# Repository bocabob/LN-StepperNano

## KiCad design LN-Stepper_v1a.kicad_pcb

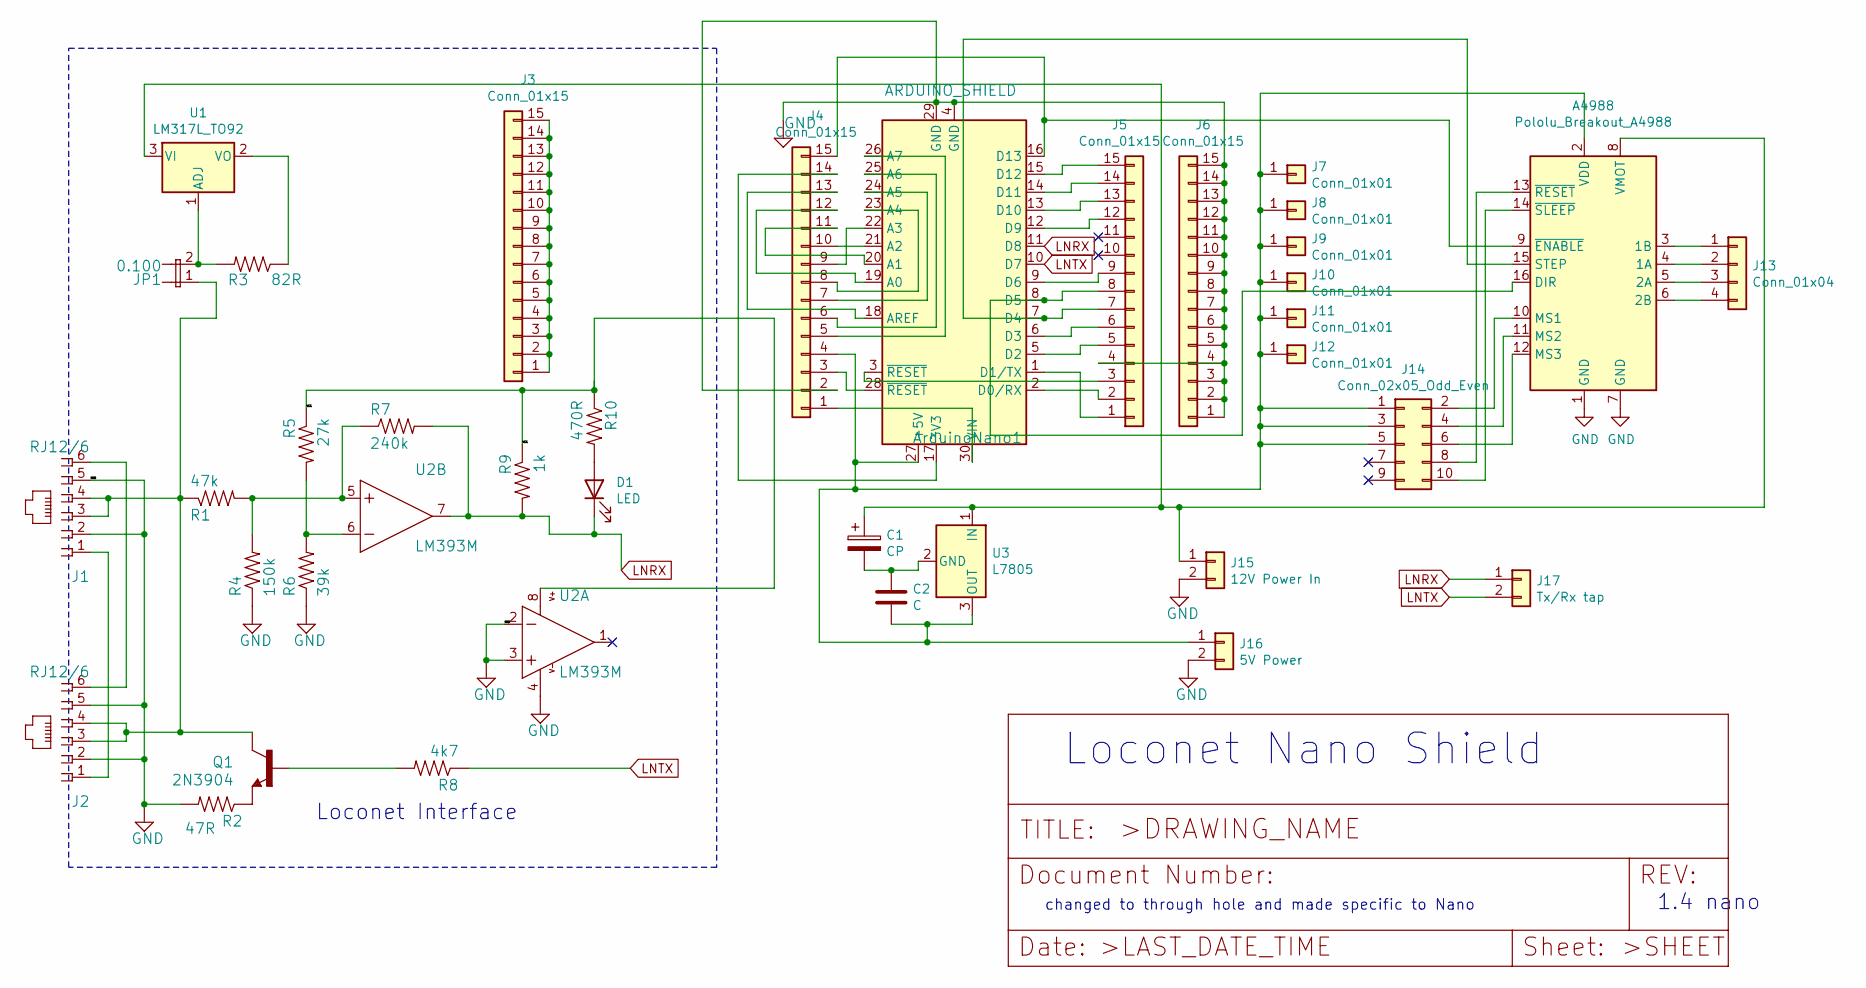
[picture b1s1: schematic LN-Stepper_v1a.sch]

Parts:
A4988: Pololu_Breakout_A4988; Pololu_Breakout-16_15.2x20.3mm
ArduinoNano1: ARDUINO_SHIELD; Arduino_Nano
C1: CP; CP_Radial_D8.0mm_P3.80mm
C2: C; CP_Radial_Tantal_D4.5mm_P5.00mm
D1: LED; LED_D5.0mm
J1, J2: RJ12/6; RJ25-PANEL
J3, J4, J5, J6: Conn_01x15; PinHeader_1x15_P2.54mm_Vertical
J7, J8, J9, J10, J11, J12: Conn_01x01; PinHeader_1x01_P2.54mm_Vertical
J13: Conn_01x04; PinSocket_1x04_P2.54mm_Vertical
J14: Conn_02x05_Odd_Even; PinHeader_2x05_P2.54mm_Vertical
J15: 12V Power In; BarrelJack_Horizontal
J16: 5V Power; TerminalBlock_Phoenix_PT-1,5-2-3.5-H_1x02_P3.50mm_Horizontal
J17: Tx/Rx tap; PinHeader_1x02_P2.54mm_Vertical
JP1: 0.100; 1X02_LOCK
Q1: 2N3904; TO-92L_Inline
R1: 47k; R_Axial_DIN0207_L6.3mm_D2.5mm_P7.62mm_Horizontal
R2: 47R; R_Axial_DIN0207_L6.3mm_D2.5mm_P7.62mm_Horizontal
R3: 82R; R_Axial_DIN0207_L6.3mm_D2.5mm_P2.54mm_Vertical
R4: 150k; R_Axial_DIN0207_L6.3mm_D2.5mm_P7.62mm_Horizontal
R5: 27k; R_Axial_DIN0207_L6.3mm_D2.5mm_P7.62mm_Horizontal
R6: 39k; R_Axial_DIN0207_L6.3mm_D2.5mm_P7.62mm_Horizontal
R7: 240k; R_Axial_DIN0207_L6.3mm_D2.5mm_P7.62mm_Horizontal
R8: 4k7; R_Axial_DIN0207_L6.3mm_D2.5mm_P7.62mm_Horizontal
R9: 1k; R_Axial_DIN0207_L6.3mm_D2.5mm_P7.62mm_Horizontal
R10: 470R; R_Axial_DIN0207_L6.3mm_D2.5mm_P7.62mm_Horizontal
U1: LM317L_TO92; TO-92_Inline
U2: LM393M; DIP-8_W7.62mm_LongPads
U3: L7805; TO-220-3_Vertical

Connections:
/VCC: R5.1, R9.1, R10.1, U2.8 (V+)
GND: A4988.1 (GND), A4988.7 (GND), ArduinoNano1.4 (GND), ArduinoNano1.29 (GND), J1.2, J1.5, J2.2, J2.5, J4.2, J5.4, J6.1, J6.2, J6.3, J6.4, J6.5, J6.6, J6.7, J6.8, J6.9, J6.10, J6.11, J6.12, J6.13, J6.14, J6.15, J15.2, J16.2, R2.2, R4.1, R6.1, U2.2 (-IN), U2.3 (+IN), U2.4 (V-)
LNRX: ArduinoNano1.11 (D8), D1.1 (K), J17.1, R7.2, R9.2, U2.7 (OUT)
LNTX: ArduinoNano1.10 (D7), J17.2, R8.1
unnamed: A4988.2 (VDD), ArduinoNano1.27 (+5V), C2.2, J4.4, J7.1, J8.1, J9.1, J10.1, J11.1, J12.1, J14.1, J14.3, J14.5, J16.1, U3.3 (OUT)
unnamed: A4988.3 (1B), J13.1
unnamed: A4988.4 (1A), J13.2
unnamed: A4988.5 (2A), J13.3
unnamed: A4988.6 (2B), J13.4
unnamed: A4988.8 (VMOT), C1.1, J15.1, U1.3 (VI), U3.1 (IN)
unnamed: A4988.9 (~ENABLE), ArduinoNano1.16 (D13), J4.15
unnamed: A4988.10 (MS1), J14.2
unnamed: A4988.11 (MS2), J14.4
unnamed: A4988.12 (MS3), J14.6
unnamed: A4988.13 (~RESET), J14.8
unnamed: A4988.14 (~SLEEP), J14.10
unnamed: A4988.15 (STEP), ArduinoNano1.7 (D4), J5.7
unnamed: A4988.16 (DIR), ArduinoNano1.8 (D5), J5.8
unnamed: ArduinoNano1.1 (D1/TX), J5.1
unnamed: ArduinoNano1.2 (D0/RX), J5.2
unnamed: ArduinoNano1.3 (~RESET), J5.3
unnamed: ArduinoNano1.5 (D2), J5.5
unnamed: ArduinoNano1.6 (D3), J5.6
unnamed: ArduinoNano1.9 (D6), J5.9
unnamed: ArduinoNano1.12 (D9), J5.12
unnamed: ArduinoNano1.13 (D10), J5.13
unnamed: ArduinoNano1.14 (D11), J5.14
unnamed: ArduinoNano1.15 (D12), J5.15
unnamed: ArduinoNano1.17 (3V3), J4.14
unnamed: ArduinoNano1.18 (AREF), J4.13
unnamed: ArduinoNano1.19 (A0), J4.12
unnamed: ArduinoNano1.20 (A1), J4.11
unnamed: ArduinoNano1.21 (A2), J4.10
unnamed: ArduinoNano1.22 (A3), J4.9
unnamed: ArduinoNano1.23 (A4), J4.8
unnamed: ArduinoNano1.24 (A5), J4.7
unnamed: ArduinoNano1.25 (A6), J4.6
unnamed: ArduinoNano1.26 (A7), J4.5
unnamed: ArduinoNano1.28 (~RESET), J4.3
unnamed: ArduinoNano1.30 (VIN), J4.1
unnamed: C1.2, C2.1, U3.2 (GND)
unnamed: D1.2 (A), R10.2
unnamed: J1.1, J2.1
unnamed: J1.3, J1.4, J2.3, J2.4, JP1.1, Q1.3 (C), R1.1
unnamed: J1.6, J2.6
unnamed: J3.1, J3.2, J3.3, J3.4, J3.5, J3.6, J3.7, J3.8, J3.9, J3.10, J3.11, J3.12, J3.13, J3.14, J3.15
unnamed: JP1.2, R3.2, U1.1 (ADJ)
unnamed: Q1.1 (B), R8.2
unnamed: Q1.2 (E), R2.1
unnamed: R1.2, R4.2, R7.1, U2.5 (+IN)
unnamed: R3.1, U1.2 (VO)
unnamed: R5.2, R6.2, U2.6 (-IN)

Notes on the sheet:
Loconet Interface
Loconet Nano Shield
1.4 nano
changed to through hole and made specific to Nano

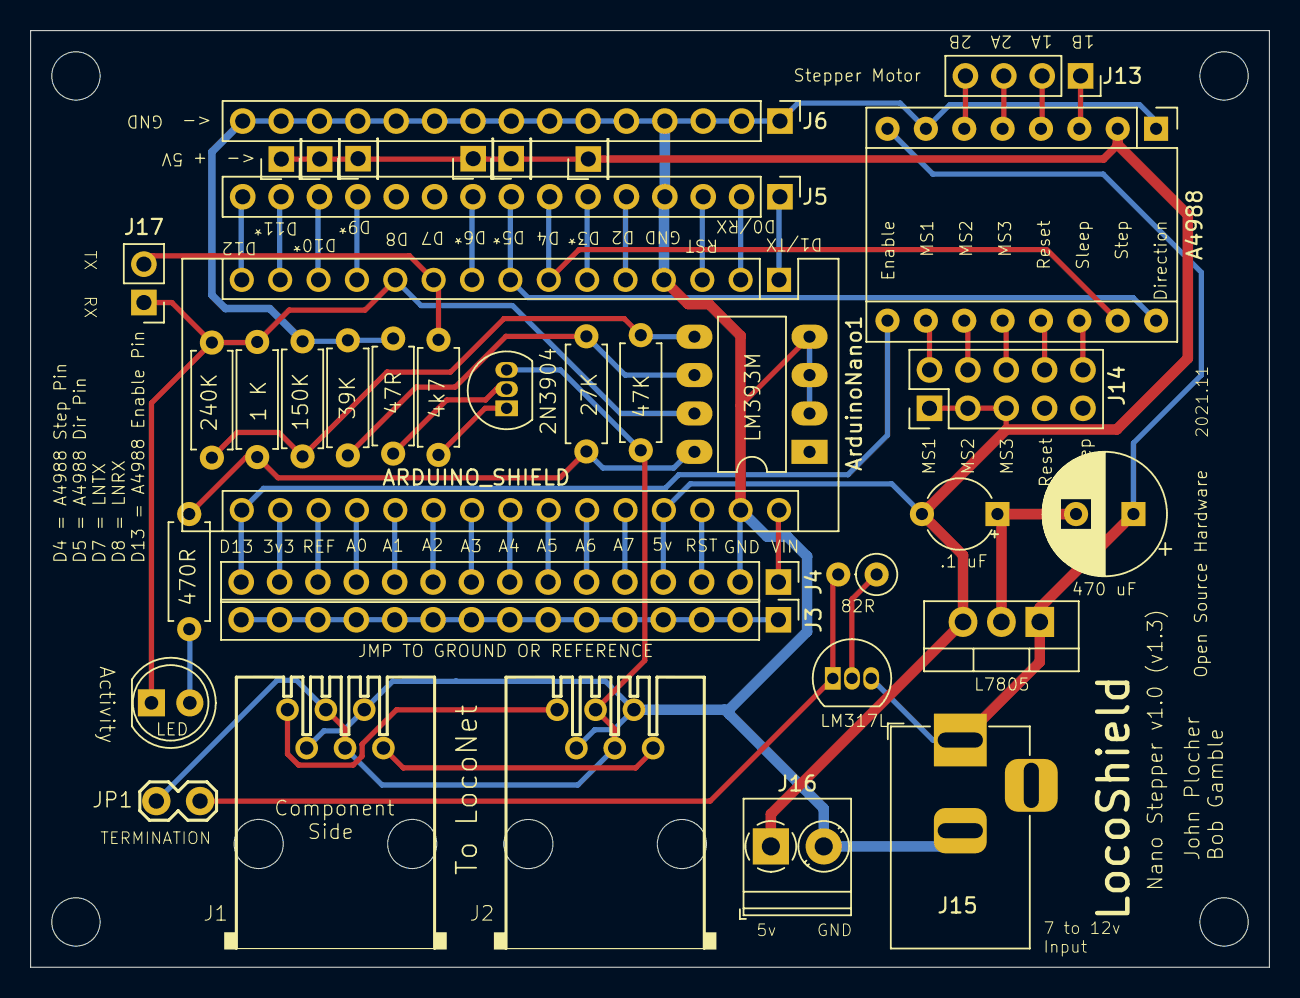
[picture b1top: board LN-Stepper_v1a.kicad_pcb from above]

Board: 2 copper layers, 82.0 x 62.0 mm, 37 parts (0 on the bottom side), 52 nets.

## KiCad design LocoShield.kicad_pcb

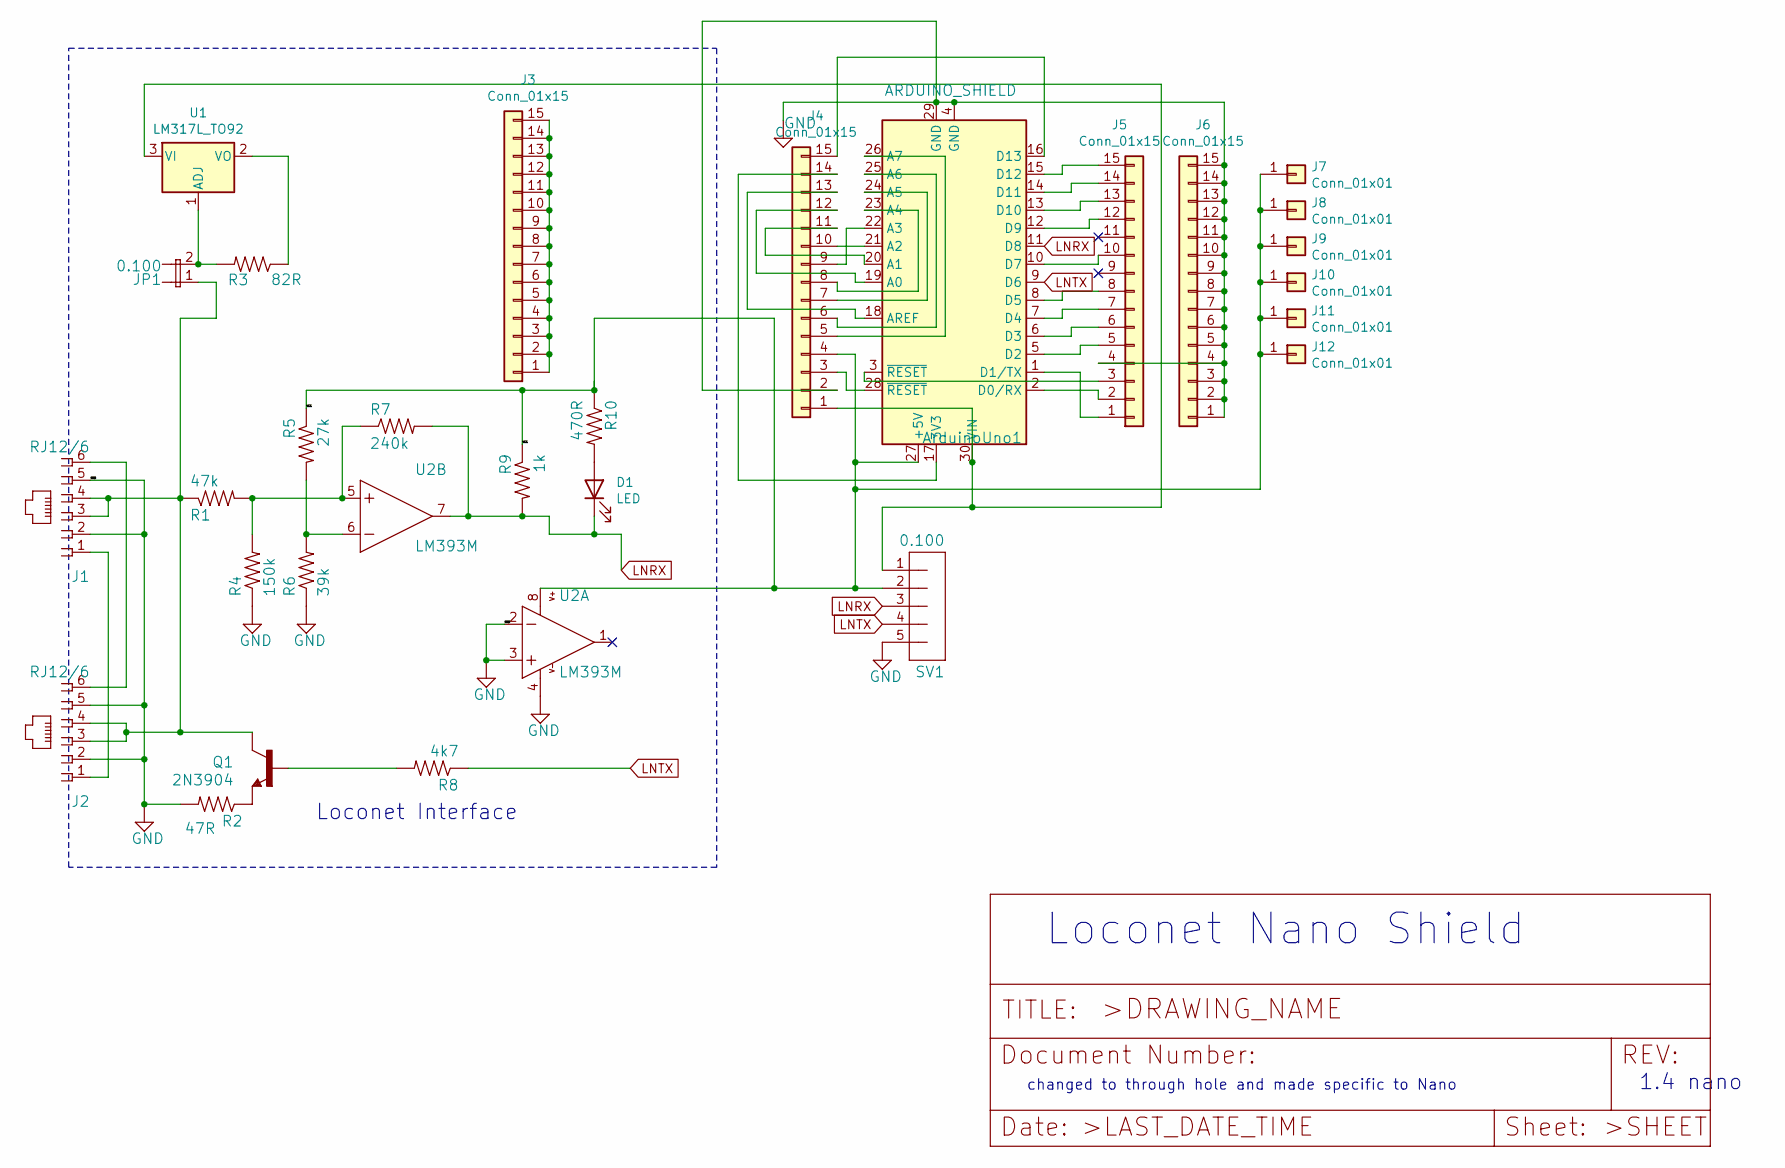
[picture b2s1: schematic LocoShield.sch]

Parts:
ArduinoUno1: ARDUINO_SHIELD; Arduino_Nano
D1: LED; LED_D5.0mm
J1, J2: RJ12/6; RJ25-PANEL
J3, J4, J5, J6: Conn_01x15; PinHeader_1x15_P2.54mm_Vertical
J7, J8, J9, J10, J11, J12: Conn_01x01; PinHeader_1x01_P2.54mm_Vertical
JP1: 0.100; 1X02_LOCK
Q1: 2N3904; TO-92L_Inline
R1: 47k; R_Axial_DIN0207_L6.3mm_D2.5mm_P2.54mm_Vertical
R2: 47R; R_Axial_DIN0207_L6.3mm_D2.5mm_P7.62mm_Horizontal
R3: 82R; R_Axial_DIN0207_L6.3mm_D2.5mm_P2.54mm_Vertical
R4: 150k; R_Axial_DIN0207_L6.3mm_D2.5mm_P7.62mm_Horizontal
R5: 27k; R_Axial_DIN0207_L6.3mm_D2.5mm_P7.62mm_Horizontal
R6: 39k; R_Axial_DIN0207_L6.3mm_D2.5mm_P7.62mm_Horizontal
R7: 240k; R_Axial_DIN0207_L6.3mm_D2.5mm_P7.62mm_Horizontal
R8: 4k7; R_Axial_DIN0207_L6.3mm_D2.5mm_P7.62mm_Horizontal
R9: 1k; R_Axial_DIN0207_L6.3mm_D2.5mm_P7.62mm_Horizontal
R10: 470R; R_Axial_DIN0207_L6.3mm_D2.5mm_P7.62mm_Horizontal
SV1: 0.100; MA05-1
U1: LM317L_TO92; TO-92_Inline
U2: LM393M; DIP-8_W7.62mm_LongPads

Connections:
/VCC: ArduinoUno1.27 (+5V), J4.4, J7.1, J8.1, J9.1, J10.1, J11.1, J12.1, R5.1, R9.1, R10.1, SV1.2, U2.8 (V+); also elsewhere on the board
GND: ArduinoUno1.4 (GND), ArduinoUno1.29 (GND), J1.2, J1.5, J2.2, J2.5, J4.2, J5.4, J6.1, J6.2, J6.3, J6.4, J6.5, J6.6, J6.7, J6.8, J6.9, J6.10, J6.11, J6.12, J6.13, J6.14, J6.15, R2.2, R4.1, R6.1, SV1.5, U2.2 (-IN), U2.3 (+IN), U2.4 (V-); also elsewhere on the board
LNRX: ArduinoUno1.11 (D8), D1.1 (K), R7.2, R9.2, SV1.3, U2.7 (OUT); also elsewhere on the board
LNTX: ArduinoUno1.9 (D6), R8.1, SV1.4; also elsewhere on the board
unnamed 4: ArduinoUno1.1 (D1/TX), J5.1; also elsewhere on the board
unnamed 5: ArduinoUno1.2 (D0/RX), J5.2; also elsewhere on the board
unnamed 6: ArduinoUno1.3 (~RESET), J5.3; also elsewhere on the board
unnamed 7: ArduinoUno1.5 (D2), J5.5; also elsewhere on the board
unnamed 8: ArduinoUno1.6 (D3), J5.6; also elsewhere on the board
unnamed 9: ArduinoUno1.7 (D4), J5.7; also elsewhere on the board
unnamed 10: ArduinoUno1.8 (D5), J5.8; also elsewhere on the board
unnamed 11: ArduinoUno1.10 (D7), J5.10; also elsewhere on the board
unnamed 12: ArduinoUno1.12 (D9), J5.12; also elsewhere on the board
unnamed 13: ArduinoUno1.13 (D10), J5.13; also elsewhere on the board
unnamed 14: ArduinoUno1.14 (D11), J5.14; also elsewhere on the board
unnamed 15: ArduinoUno1.15 (D12), J5.15; also elsewhere on the board
unnamed 16: ArduinoUno1.16 (D13), J4.15; also elsewhere on the board
unnamed 17: ArduinoUno1.17 (3V3), J4.14; also elsewhere on the board
unnamed 18: ArduinoUno1.18 (AREF), J4.13; also elsewhere on the board
unnamed 19: ArduinoUno1.19 (A0), J4.12; also elsewhere on the board
unnamed 20: ArduinoUno1.20 (A1), J4.11; also elsewhere on the board
unnamed 21: ArduinoUno1.21 (A2), J4.10; also elsewhere on the board
unnamed 22: ArduinoUno1.22 (A3), J4.9; also elsewhere on the board
unnamed 23: ArduinoUno1.23 (A4), J4.8; also elsewhere on the board
unnamed 24: ArduinoUno1.24 (A5), J4.7; also elsewhere on the board
unnamed 25: ArduinoUno1.25 (A6), J4.6; also elsewhere on the board
unnamed 26: ArduinoUno1.26 (A7), J4.5; also elsewhere on the board
unnamed 27: ArduinoUno1.28 (~RESET), J4.3; also elsewhere on the board
unnamed 28: ArduinoUno1.30 (VIN), J4.1, SV1.1, U1.3 (VI); also elsewhere on the board
unnamed: D1.2 (A), R10.2
unnamed: J1.1, J2.1
unnamed: J1.3, J1.4, J2.3, J2.4, JP1.1, Q1.3 (C), R1.1
unnamed: J1.6, J2.6
unnamed: J3.1, J3.2, J3.3, J3.4, J3.5, J3.6, J3.7, J3.8, J3.9, J3.10, J3.11, J3.12, J3.13, J3.14, J3.15
unnamed: JP1.2, R3.2, U1.1 (ADJ)
unnamed: Q1.1 (B), R8.2
unnamed: Q1.2 (E), R2.1
unnamed: R1.2, R4.2, R7.1, U2.5 (+IN)
unnamed: R3.1, U1.2 (VO)
unnamed: R5.2, R6.2, U2.6 (-IN)

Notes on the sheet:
Loconet Interface
Loconet Nano Shield
1.4 nano
changed to through hole and made specific to Nano

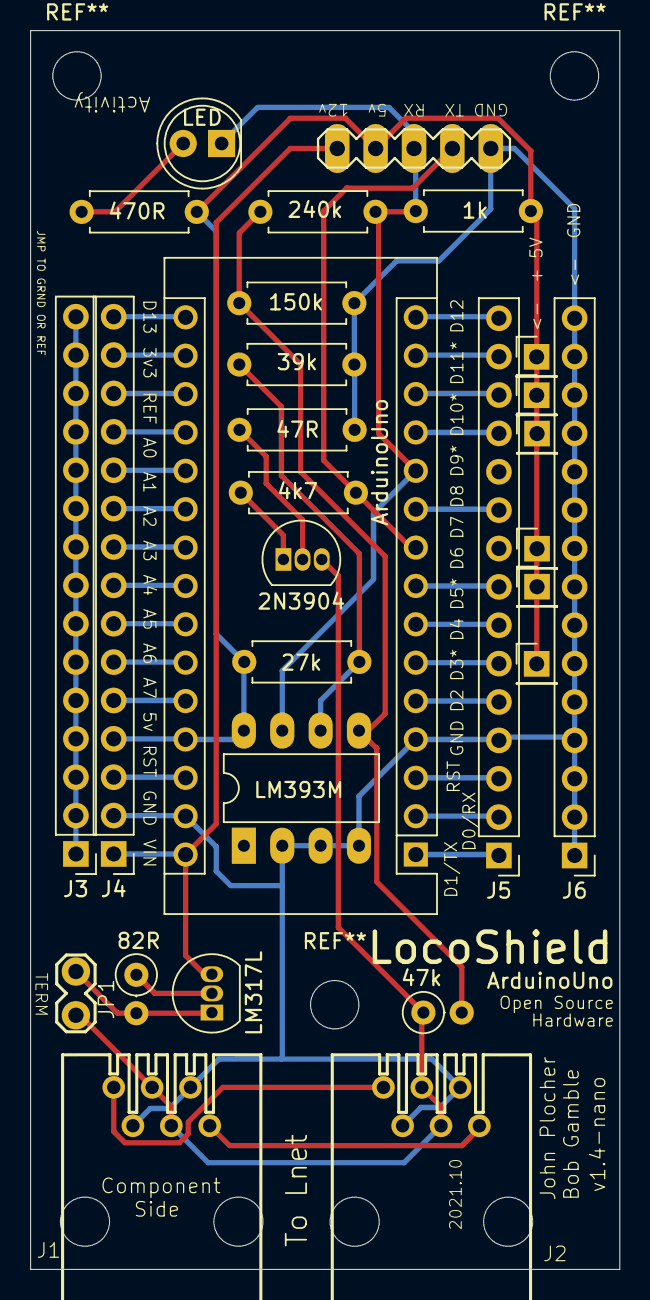
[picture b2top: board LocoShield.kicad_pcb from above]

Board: 2 copper layers, 39.0 x 82.0 mm, 29 parts (0 on the bottom side), 40 nets.

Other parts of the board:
ArduinoUno: ARDUINO_SHIELD; Arduino_Nano

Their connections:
/VCC: ArduinoUno.27; also elsewhere on the board
GND: ArduinoUno.4, ArduinoUno.29; also elsewhere on the board
LNRX: ArduinoUno.11; also elsewhere on the board
LNTX: ArduinoUno.9; also elsewhere on the board
unnamed 4: ArduinoUno.1; also elsewhere on the board
unnamed 5: ArduinoUno.2; also elsewhere on the board
unnamed 6: ArduinoUno.3; also elsewhere on the board
unnamed 7: ArduinoUno.5; also elsewhere on the board
unnamed 8: ArduinoUno.6; also elsewhere on the board
unnamed 9: ArduinoUno.7; also elsewhere on the board
unnamed 10: ArduinoUno.8; also elsewhere on the board
unnamed 11: ArduinoUno.10; also elsewhere on the board
unnamed 12: ArduinoUno.12; also elsewhere on the board
unnamed 13: ArduinoUno.13; also elsewhere on the board
unnamed 14: ArduinoUno.14; also elsewhere on the board
unnamed 15: ArduinoUno.15; also elsewhere on the board
unnamed 16: ArduinoUno.16; also elsewhere on the board
unnamed 17: ArduinoUno.17; also elsewhere on the board
unnamed 18: ArduinoUno.18; also elsewhere on the board
unnamed 19: ArduinoUno.19; also elsewhere on the board
unnamed 20: ArduinoUno.20; also elsewhere on the board
unnamed 21: ArduinoUno.21; also elsewhere on the board
unnamed 22: ArduinoUno.22; also elsewhere on the board
unnamed 23: ArduinoUno.23; also elsewhere on the board
unnamed 24: ArduinoUno.24; also elsewhere on the board
unnamed 25: ArduinoUno.25; also elsewhere on the board
unnamed 26: ArduinoUno.26; also elsewhere on the board
unnamed 27: ArduinoUno.28; also elsewhere on the board
unnamed 28: ArduinoUno.30; also elsewhere on the board

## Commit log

2022-06-25 moved old files
    moved prior board versions to old files folder for clarity
